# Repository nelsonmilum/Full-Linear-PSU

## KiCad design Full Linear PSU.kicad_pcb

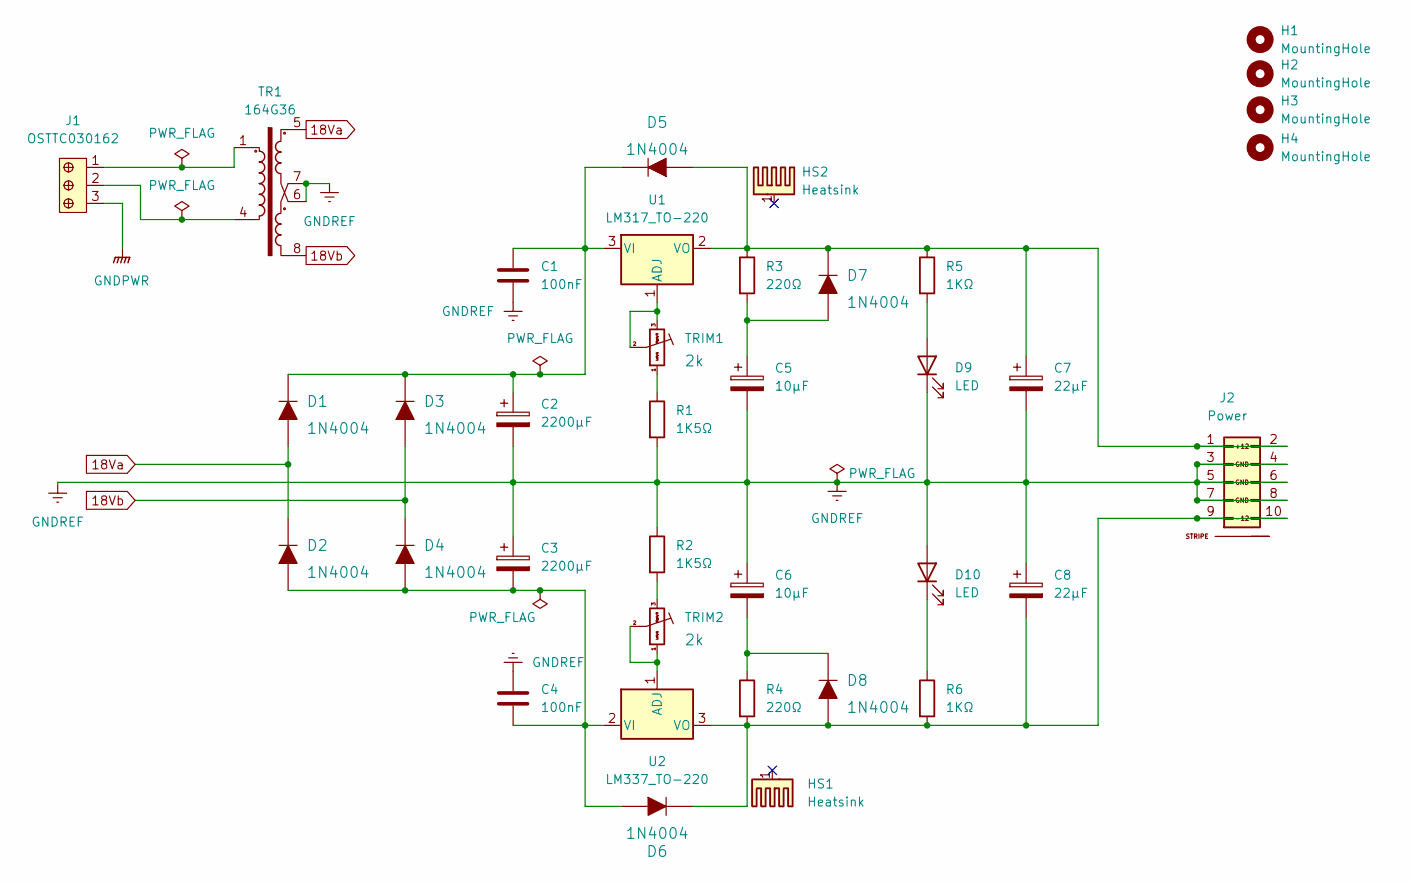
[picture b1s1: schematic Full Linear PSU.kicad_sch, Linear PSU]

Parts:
C1, C4: 100nF; C_Rect_L4.6mm_W2.0mm_P2.50mm_MKS02_FKP02
C2, C3: 2200µF; CP_Radial_D12.5mm_P5.00mm; Part EEU-HD1V222B
C5, C6: 10µF; CP_Radial_D8.0mm_P5.00mm
C7, C8: 22µF; CP_Radial_D8.0mm_P5.00mm
D1, D2, D3, D4, D5, D6, D7, D8: 1N4004; DO-41; MPN 1N4004-T; Digi-Key_PN 1N4004DICT-ND
D9, D10: LED; LED_D3.0mm
H1, H2, H3, H4: MountingHole; MountingHole_3.2mm_M3_DIN965
HS1, HS2: Heatsink; HS346-ND; MPN 513102B02500G
J1: OSTTC030162; Term_Block_1x3_P5mm; MPN OSTTC030162; Digi-Key_PN ED2601-ND
J2: Power; Pins_2x05_2.54mm_TH_Europower; Part Number 1-1002FBV0T
R1, R2: 1K5Ω; R_Axial_DIN0207_L6.3mm_D2.5mm_P10.16mm_Horizontal
R3, R4: 220Ω; R_Axial_DIN0207_L6.3mm_D2.5mm_P10.16mm_Horizontal
R5, R6: 1KΩ; R_Axial_DIN0207_L6.3mm_D2.5mm_P10.16mm_Horizontal
TR1: 164G36
TRIM1, TRIM2: TrimPot_3299Y_2k; Potentiometer_Bourns_3299Y_Vertical; Part Number 3299Y-1-202LF
U1: LM317_TO-220; TO-220F-3_Vertical
U2: LM337_TO-220; TO-220F-3_Vertical

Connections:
18Va: D1.A, D2.K, TR1.5
18Vb: D3.A, D4.K, TR1.8
GNDPWR: J1.3
GNDREF: C1.2, C2.2, C3.1, C4.1, C5.2, C6.1, C7.2, C8.1, D9.1 (K), D10.2 (A), J2.3 (GND), J2.4 (GND), J2.5 (GND), J2.6 (GND), J2.7 (GND), J2.8 (GND), R1.2, R2.1, TR1.6, TR1.7
unnamed: C1.1, C2.1, D1.K, D3.K, D5.K, U1.3 (VI)
unnamed: C3.2, C4.2, D2.A, D4.A, D6.A, U2.2 (VI)
unnamed: C5.1, D7.A, R3.2
unnamed: C6.2, D8.K, R4.1
unnamed: C7.1, D5.A, D7.K, J2.1 (+12V), J2.2 (+12V), R3.1, R5.1, U1.2 (VO)
unnamed: C8.2, D6.K, D8.A, J2.9 (-12V), J2.10 (-12V), R4.2, R6.2, U2.3 (VO)
unnamed: D9.2 (A), R5.2
unnamed: D10.1 (K), R6.1
unnamed: J1.1, TR1.1
unnamed: J1.2, TR1.4
unnamed: R1.1, TRIM1.1 (Left)
unnamed: R2.2, TRIM2.3 (Right)
unnamed: TRIM1.2 (Center), TRIM1.3 (Right), U1.1 (ADJ)
unnamed: TRIM2.1 (Left), TRIM2.2 (Center), U2.1 (ADJ)

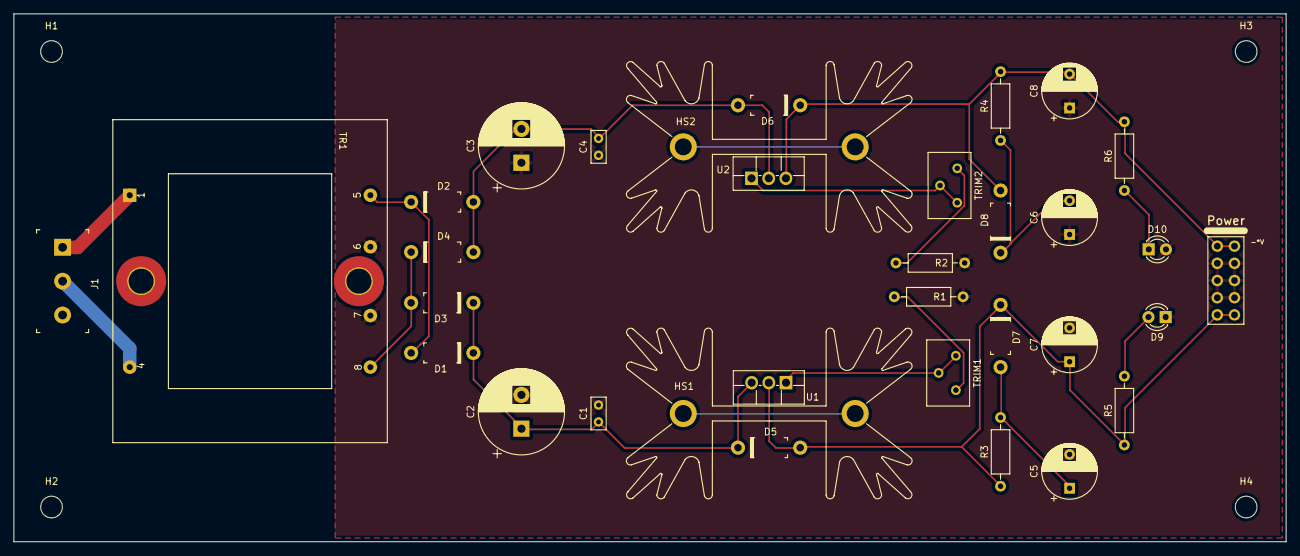
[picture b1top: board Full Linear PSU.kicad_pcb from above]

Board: 2 copper layers, 188.0 x 78.0 mm, 37 parts (0 on the bottom side), 17 nets.

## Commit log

2022-01-04 init
2022-01-04 reinit
2022-01-04 recommit

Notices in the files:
Full Linear PSU.kicad_pcb:
CC-BY-NC
